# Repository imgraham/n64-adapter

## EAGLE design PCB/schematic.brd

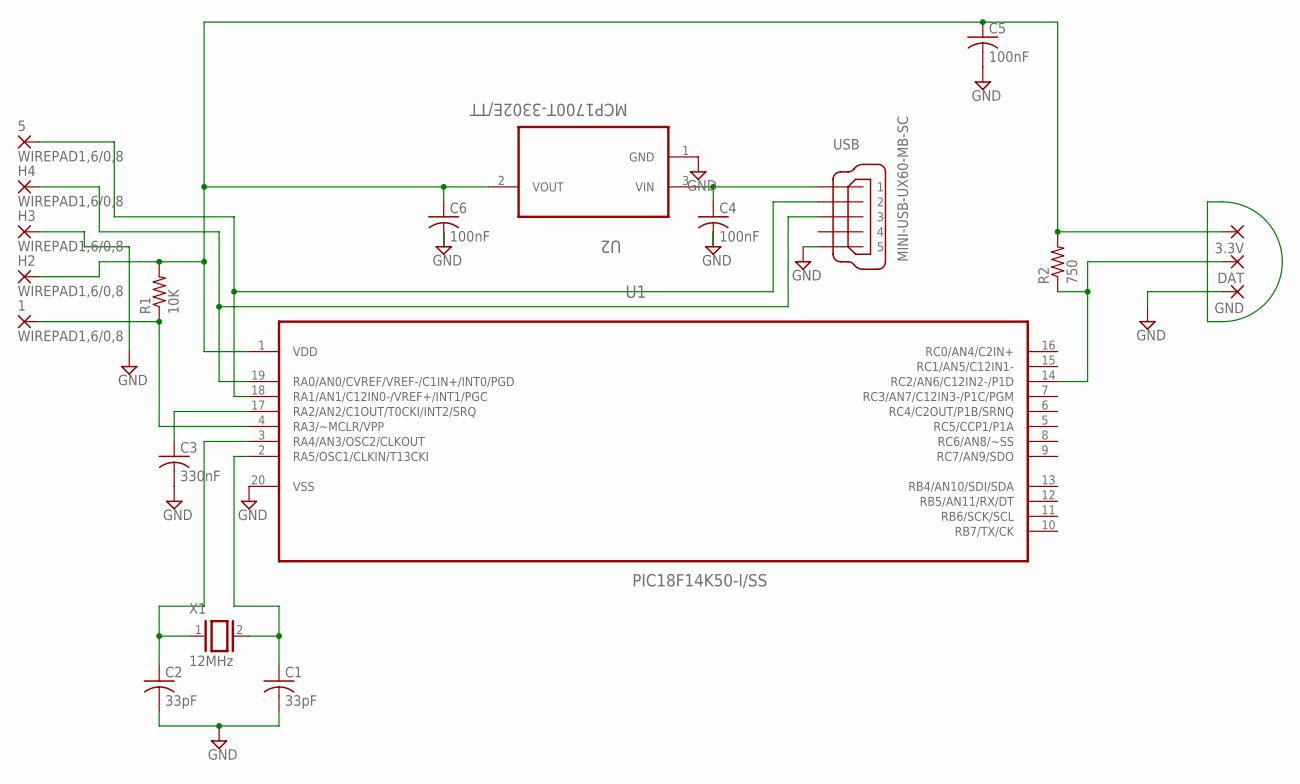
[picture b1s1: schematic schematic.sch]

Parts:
1, 5: WIREPAD1,6/0,8; 1,6/0,8
3.3V: SMD2; SMD1,27-2,54
C1, C2: 33pF; C0402
C3: 330nF; C0603
C4, C5, C6: 100nF; C0402
DAT: SMD2; SMD1,27-2,54
GND: SMD2; SMD1,27-2,54
H2, H3, H4: WIREPAD1,6/0,8; 1,6/0,8
R1: 10K; R0805
R2: 750; R0805
U1: PIC18F14K50-I/SS; SOP65P780X200-20N
U2: MCP1700T-3302E/TT; SOT95P237X112-3N
USB: MINI-USB-UX60-MB-SC; UX60-MB-SC
X1: 12MHz; QS

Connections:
GND: C1.2, C2.2, C3.2, C4.2, C5.2, C6.2, GND.1, H3.1, U1.20 (VSS), U2.1 (GND), USB.P$5 (5)
unnamed: C4.1, U2.3 (VIN), USB.P$1 (1)
unnamed: 3.3V.1, C5.1, C6.1, H2.1, R1.2, R2.2, U1.1 (VDD), U2.2 (VOUT)
unnamed: 1.1, R1.1, U1.4 (RA3/~MCLR/VPP)
unnamed: C3.1, U1.17 (RA2/AN2/C1OUT/T0CKI/INT2/SRQ)
unnamed: C1.1, U1.2 (RA5/OSC1/CLKIN/T13CKI), X1.2
unnamed: C2.1, U1.3 (RA4/AN3/OSC2/CLKOUT), X1.1
unnamed: DAT.1, R2.1, U1.14 (RC2/AN6/C12IN2-/P1D)
unnamed: 5.1, U1.18 (RA1/AN1/C12IN0-/VREF+/INT1/PGC), USB.P$2 (2)
unnamed: H4.1, U1.19 (RA0/AN0/CVREF/VREF-/C1IN+/INT0/PGD), USB.P$3 (3)

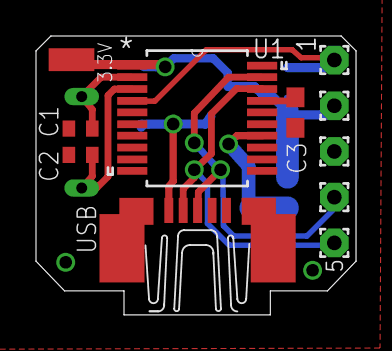
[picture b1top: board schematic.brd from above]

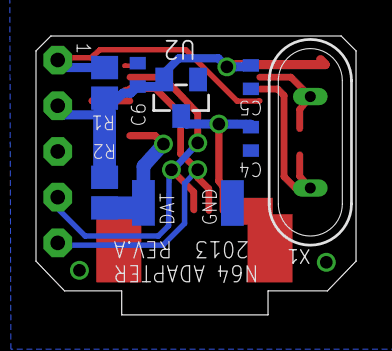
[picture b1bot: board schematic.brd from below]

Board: 2 copper layers, 17.8 x 15.5 mm, 20 parts (9 on the bottom side), 10 nets.

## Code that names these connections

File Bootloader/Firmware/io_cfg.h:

/*********************************************************************
 *
 *                Microchip USB C18 Firmware 
 *
 *********************************************************************
 * FileName:        io_cfg.h
 * Dependencies:    See INCLUDES section below
 * Processor:       PIC18
 * Compiler:        C18 3.11+
 * Company:         Microchip Technology, Inc.
 *
 * Software License Agreement
 *
 * The software supplied herewith by Microchip Technology Incorporated
 * (the �Company�) for its PICmicro� Microcontroller is intended and
 * supplied to you, the Company�s customer, for use solely and
 * exclusively on Microchip PICmicro Microcontroller products. The
 * software is owned by the Company and/or its supplier, and is
 * protected under applicable copyright laws. All rights are reserved.
 * Any use in violation of the foregoing restrictions may subject the
 * user to criminal sanctions under applicable laws, as well as to
 * civil liability for the breach of the terms and conditions of this
 * license.
 *
 * THIS SOFTWARE IS PROVIDED IN AN �AS IS� CONDITION. NO WARRANTIES,
 * WHETHER EXPRESS, IMPLIED OR STATUTORY, INCLUDING, BUT NOT LIMITED
 * TO, IMPLIED WARRANTIES OF MERCHANTABILITY AND FITNESS FOR A
 * PARTICULAR PURPOSE APPLY TO THIS SOFTWARE. THE COMPANY SHALL NOT,
 * IN ANY CIRCUMSTANCES, BE LIABLE FOR SPECIAL, INCIDENTAL OR
 * CONSEQUENTIAL DAMAGES, FOR ANY REASON WHATSOEVER.
 *
 * File Version  Date		Comment
 *~~~~~~~~~~~~~~~~~~~~~~~~~~~~~~~~~~~~~~~~~~~~~~~~~~~~~~~~~~~~~~~~~~~~
 * 1.0			 04/09/2008	Started from MCHPFSUSB v1.3 HID Mouse
 *							demo project.  Commented out items that
 *							are not particularly useful for the
 *							bootloader.
 ********************************************************************/

#ifndef IO_CFG_H
#define IO_CFG_H

/** I N C L U D E S *************************************************/
#include "usbcfg.h"

/** T R I S *********************************************************/
#define INPUT_PIN           1
#define OUTPUT_PIN          0

#if defined(PIC18F4550_PICDEM_FS_USB)
/** U S B ***********************************************************/
#define tris_usb_bus_sense  TRISAbits.TRISA1    // Input

#if defined(USE_USB_BUS_SENSE_IO)
#define usb_bus_sense       PORTAbits.RA1
#else
#define usb_bus_sense       1
#endif

#define tris_self_power     TRISAbits.TRISA2    // Input

#if defined(USE_SELF_POWER_SENSE_IO)
#define self_power          PORTAbits.RA2
#else
#define self_power          1
#endif

// External Transceiver Interface
#define tris_usb_vpo        TRISBbits.TRISB3    // Output
#define tris_usb_vmo        TRISBbits.TRISB2    // Output
#define tris_usb_rcv        TRISAbits.TRISA4    // Input
#define tris_usb_vp         TRISCbits.TRISC5    // Input
#define tris_usb_vm         TRISCbits.TRISC4    // Input
#define tris_usb_oe         TRISCbits.TRISC1    // Output

#define tris_usb_suspnd     TRISAbits.TRISA3    // Output

/** L E D ***********************************************************/
#define mInitAllLEDs()      LATD &= 0xF0; TRISD &= 0xF0;

#define mLED_1              LATDbits.LATD0
#define mLED_2              LATDbits.LATD1
#define mLED_3              LATDbits.LATD2
#define mLED_4              LATDbits.LATD3

#define mLED_1_On()         mLED_1 = 1;
#define mLED_2_On()         mLED_2 = 1;
#define mLED_3_On()         mLED_3 = 1;
#define mLED_4_On()         mLED_4 = 1;

#define mLED_1_Off()        mLED_1 = 0;
#define mLED_2_Off()        mLED_2 = 0;
#define mLED_3_Off()        mLED_3 = 0;
#define mLED_4_Off()        mLED_4 = 0;

#define mLED_1_Toggle()     mLED_1 = !mLED_1;
#define mLED_2_Toggle()     mLED_2 = !mLED_2;
#define mLED_3_Toggle()     mLED_3 = !mLED_3;
#define mLED_4_Toggle()     mLED_4 = !mLED_4;

/** S W I T C H *****************************************************/
#define mInitAllSwitches()  TRISBbits.TRISB4=1;TRISBbits.TRISB5=1;
#define mInitSwitch2()      TRISBbits.TRISB4=1;
#define mInitSwitch3()      TRISBbits.TRISB5=1;
#define sw2                 PORTBbits.RB4
#define sw3                 PORTBbits.RB5

/** P O T ***********************************************************/
#define mInitPOT()          TRISAbits.TRISA0=1;ADCON0=0x01;ADCON2=0x3C;

/** S P I : Chip Select Lines ***************************************/
#define tris_cs_temp_sensor TRISBbits.TRISB2    // Output
#define cs_temp_sensor      LATBbits.LATB2

#define tris_cs_sdmmc       TRISBbits.TRISB3    // Output
#define cs_sdmmc            LATBbits.LATB3

/** S D M M C *******************************************************/
#define TRIS_CARD_DETECT    TRISBbits.TRISB4    // Input
#define CARD_DETECT         PORTBbits.RB4

#define TRIS_WRITE_DETECT   TRISAbits.TRISA4    // Input
#define WRITE_DETECT        PORTAbits.RA4

/********************************************************************/
/********************************************************************/
/********************************************************************/



#elif defined(LOW_PIN_COUNT_USB_DEVELOPMENT_KIT)
	//Uncomment the below line(s) if the hardware supports it and
	//it is desireable to use one or both of the features.
	//#define USE_SELF_POWER_SENSE_IO	
	//#define USE_USB_BUS_SENSE_IO

    #define tris_usb_bus_sense  TRISAbits.TRISA1    // Input


	#if defined(USE_USB_BUS_SENSE_IO)
	#define usb_bus_sense       PORTAbits.RA1
	#else
	#define usb_bus_sense       1
	#endif
	
	#define tris_self_power     TRISAbits.TRISA2    // Input
	
	#if defined(USE_SELF_POWER_SENSE_IO)
	#define self_power          PORTAbits.RA2
	#else
	#define self_power          1
	#endif

    
    /** LED ************************************************************/
    #define mInitAllLEDs()      LATC &= 0xF0; TRISC &= 0xF0;
    
    #define mLED_1              LATCbits.LATC0
    #define mLED_2              LATCbits.LATC1
    #define mLED_3              LATCbits.LATC2
    #define mLED_4              LATCbits.LATC3
    
    #define mLED_1_On()         mLED_1 = 1;
    #define mLED_2_On()         mLED_2 = 1;
    #define mLED_3_On()         mLED_3 = 1;
    #define mLED_4_On()         mLED_4 = 1;
    
    #define mLED_1_Off()        mLED_1 = 0;
    #define mLED_2_Off()        mLED_2 = 0;
    #define mLED_3_Off()        mLED_3 = 0;
    #define mLED_4_Off()        mLED_4 = 0;
    
    #define mLED_1_Toggle()     mLED_1 = !mLED_1;
    #define mLED_2_Toggle()     mLED_2 = !mLED_2;
    #define mLED_3_Toggle()     mLED_3 = !mLED_3;
    #define mLED_4_Toggle()     mLED_4 = !mLED_4;
    
    /** SWITCH *********************************************************/
    #define mInitSwitch2()      //TRISAbits.TRISA3=1
        //only one switch available so double duty
    #define mInitSwitch3()      //TRISAbits.TRISA3=1
    #define sw2                 PORTCbits.RC2
    #define sw3                 PORTCbits.RC2
    #define mInitAllSwitches()  mInitSwitch2();
    
    /** POT ************************************************************/
    #define mInitPOT()          {TRISBbits.TRISB4=1;ADCON0=0x29;ADCON1=0;ADCON2=0x3E;ADCON2bits.ADFM = 1;}





//Uncomment below if using the YOUR_BOARD hardware platform
//#elif defined(YOUR_BOARD)
//Add your hardware specific I/O pin mapping here

#else
    #error Not a supported board (yet), add I/O pin mapping in __FILE__, line __LINE__
#endif

#endif //IO_CFG_H

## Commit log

2013-09-21 Code Cleanup
2013-09-21 Git tracking cleanup
2013-09-23 Updated comments and cleaned up formatting Optimized USB code to read gamepad values more efficiently Removed unused debug files
2013-09-24 Further optimization - Removed unused USB variables - Unused ports set up as outputs for better practice - User variable space rearranged
2013-09-24 Adapter now detects controller being unplugged and zeroes values
2016-03-30 Move firmware to its own folder
2016-03-30 Change default build config to 18F14K50, add vector remapping for bootloader
2016-03-30 Added bootloader files
2016-03-30 Added solidworks files to source control
2016-03-30 Add comments for clarity
2016-03-30 Added Case V2 Files
2016-03-30 Added PCB Files
2016-03-30 Remove old PCB files, Update project to latest Eagle version
2016-03-30 Make project build
2016-03-30 Clean up assembly and change hat position logic to save a lot of codespace
2016-03-30 Clean up assembly a bit to remove unneeded instructions
2016-03-30 Clean up main
2016-03-30 Remove random buffer, change controller_data_error to regular variable
2016-03-31 Reduce asm instructions, clean up c code a bit more
2016-03-31 PollController returns value instead of using a global
2016-04-02 Cleaned up code for sending data - can now send arbitrary bytes
2016-04-02 Properly send stop bit
2016-04-02 Changed comm functions to be more generic - SendCommand, ReadData with params passed in instead of global variables
